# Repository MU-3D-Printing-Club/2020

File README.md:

# 2020
Meetings 2pm Thursday in E3508.

[Link to Ada Assembly instructions](https://openbionicslabs.com/obtutorials/ada-v1-assembly)

## Updates 2/27/2020
- Please remember to always **PULL FROM ORIGIN** and make a new branch before you make edits.
- Installed gitHub, Eagle, and SolidWorks on lab computer

## V2
Stuart's ARM board and probably Rust code.
- [x] Ask Dr. Gillis for review. (JD)
- [ ] Get rust code running for servos on discovery board. PWM libraries and also [potentiometer controlled feedback](https://www.actuonix.com/Actuonix-PQ-12-P-Linear-Actuator-p/pq12-p.htm). (Chris/Jake/Stuart/James/Matt)
- [x] Identify which rust-compatible chip to buy. (Jake/Stuart)
## V1
### V1.3 

Added [boost regulator](http://ww1.microchip.com/downloads/en/DeviceDoc/20005572A.pdf) in addition to 1.2 changes.  
- [ ] Review Ahmad's suggestions. Look in "Regulator" branch. (Jake/Ethan)
- [ ] Make Vcc route bigger.
### V1.2
Added [LiPo](https://cdn.sparkfun.com/assets/learn_tutorials/6/9/5/MCP738312.pdf) charger.

- [ ] Solder chip and resistors on.
- [ ] Burn bootloader and code. See if it works.
- [ ] Research new trigger algorithm. (James/Matt)
- [ ] Research custom myoelectric sensor. (Rosie)
- [ ] PALM DESIGN! (Chris, Hannah, Colm)
### V1.1
Reorganized PCB. Larger back cover.

- [ ] Document
- [ ] SHIP.
- [x] Tie knots. (Jack)
- [x] Solder myoelectric in.
- [x] Attach servos.
- [x] Print back cover.
- [x] Epoxy screw in.
- [x] Get the programmer out of reset mode. (Stuart)

### V1.0
From December. Broke because of lack and space/organization in back cover.

## V0
Bare bones code and prototype back cover. Cannot find Eagle file. Only legend speaks of this.

<pre>
.
├── Datasheets
│   ├── Actuonix+PQ12+Datasheet.pdf
│   ├── MCP73831.pdf
│   └── STM32F303.pdf
├── Myosensor
│   ├── Myosense.v1.brd
│   └── Myosense.v1.sch
├── Old
│   ├── Eagle Libraries
│   │   └── 3DPC.lbr
│   ├── Jig Components
│   │   ├── Legiment Jig.SLDPRT
│   │   └── Legiment Jig.STL
│   ├── eletronics test bed
│   │   ├── 400 point breadboard holder.stl
│   │   ├── STM32F3DISCOVERY holder.stl
│   │   ├── actuonix PQ12 servo holder.stl
│   │   ├── battery holder.stl
│   │   └── electronics v1.0 holder.stl
│   ├── v0.0
│   │   ├── SolidWorks
│   │   │   ├── Backcover 12-6-19.SLDPRT
│   │   │   └── Backcover 12-6-19.STL
│   │   ├── myoFlex-Original
│   │   │   └── myoFlex.ino
│   │   └── pcb
│   │       ├── circuitdraft.brd
│   │       ├── circuitdraft.sch
│   │       └── eagle.epf
│   ├── v0.1
│   │   └── PCB
│   │       ├── circuitdraft.brd
│   │       ├── circuitdraft.sch
│   │       └── eagle.epf
│   ├── v1.0
│   │   ├── PCB
│   │   │   ├── circuitdraft.brd
│   │   │   ├── circuitdraft.sch
│   │   │   └── eagle.epf
│   │   ├── PCB Libraries
│   │   │   ├── SamacSys_Parts.lbr
│   │   │   ├── TPS54627DDAR.lbr
│   │   │   ├── charger.lbr
│   │   │   ├── ind2.lbr
│   │   │   ├── inductor.lbr
│   │   │   ├── mega32U4.lbr
│   │   │   ├── microchip-update.lbr
│   │   │   └── powerPad.lbr
│   │   ├── SolidWorks
│   │   │   ├── 191216_Backcover_JD.SLDPRT
│   │   │   └── 191216_Backcover_JD.STL
│   │   ├── circuitdraft.txt
│   │   └── mainCode
│   │       └── mainCode.ino
│   ├── v1.1
│   │   ├── CAD
│   │   │   ├── 02_18_2020_BackcoverC.SLDPRT
│   │   │   ├── 02_18_2020_BackcoverF.SLDPRT
│   │   │   ├── 02_18_2020_BackcoverF.STL
│   │   │   ├── 2020_03_02_BackcoverShell.SLDPRT
│   │   │   ├── 203101_Backcover.SLDPRT
│   │   │   ├── Front Face Palm Screen Capture.PNG
│   │   │   ├── New Palm STL.STL
│   │   │   ├── New Palm.SLDPRT
│   │   │   ├── R_palm.SLDPRT
│   │   │   └── R_palm.stl
│   │   ├── Code
│   │   │   ├── Blink
│   │   │   │   └── Blink.ino
│   │   │   ├── helloWorld
│   │   │   │   └── helloWorld.ino
│   │   │   ├── mainCode
│   │   │   │   └── mainCode.ino
│   │   │   └── servoTest
│   │   │       └── servoTest.ino
│   │   └── PCB
│   │       ├── circuitdraft.brd
│   │       ├── circuitdraft.sch
│   │       └── eagle.epf
│   ├── v1.2
│   │   ├── Notes.txt
│   │   ├── PCB
│   │   │   ├── circuitdraft.brd
│   │   │   ├── circuitdraft.sch
│   │   │   └── eagle.epf
│   │   ├── mainCode
│   │   │   └── mainCode.ino
│   │   └── testLiPoCharger
│   │       └── testLiPoCharger.ino
│   ├── v1.3
│   │   ├── circuitdraft.brd
│   │   └── circuitdraft.sch
│   ├── v2.0
│   │   └── PCB
│   │       ├── Hand v2.0 parts.lib
│   │       ├── Hand v2.0-cache.lib
│   │       ├── Hand v2.0-rescue.dcm
│   │       ├── Hand v2.0.kicad_pcb
│   │       ├── Hand v2.0.kicad_pcb-bak
│   │       ├── Hand v2.0.net
│   │       ├── Hand v2.0.sch
│   │       ├── Hand v2.0.sch-bak
│   │       ├── fp-info-cache
│   │       ├── hand parts.bck
│   │       ├── hand parts.dcm
│   │       └── sym-lib-table
│   └── v2.1
│       └── PCB
│           ├── 2020-02-01_02-22-13
│           │   ├── 2020-02-01_02-22-13.lib
│           │   ├── footprints.pretty
│           │   │   └── STM32F302_303C2.kicad_mod
│           │   └── readme.txt
│           ├── Hand v2.1 parts.lib
│           ├── Hand v2.1-cache.lib
│           ├── Hand v2.1-rescue.dcm
│           ├── Hand v2.1-rescue.lib
│           ├── Hand v2.1.kicad_pcb
│           ├── Hand v2.1.kicad_pcb-bak
│           ├── Hand v2.1.net
│           ├── Hand v2.1.sch
│           ├── Hand v2.1.sch-bak
│           ├── fp-info-cache
│           ├── hand parts.bck
│           ├── hand parts.dcm
│           └── sym-lib-table
├── README.md
├── tree.txt
├── treeCMD.txt
└── v3.0
    └── hand v3.0
        ├── Hand Parts.bck
        ├── Hand Parts.dcm
        ├── Hand Parts.lib
        ├── fp-info-cache
        ├── hand v3.0-cache.lib
        ├── hand v3.0.kicad_pcb
        ├── hand v3.0.sch
        ├── hand v3.0.sch-bak
        ├── hand v3.xml
        └── sym-lib-table

38 directories, 103 files

</pre>
tree -I "*.pro|*.b#?|*.s#?|*.l?|*.job" -o tree.txt

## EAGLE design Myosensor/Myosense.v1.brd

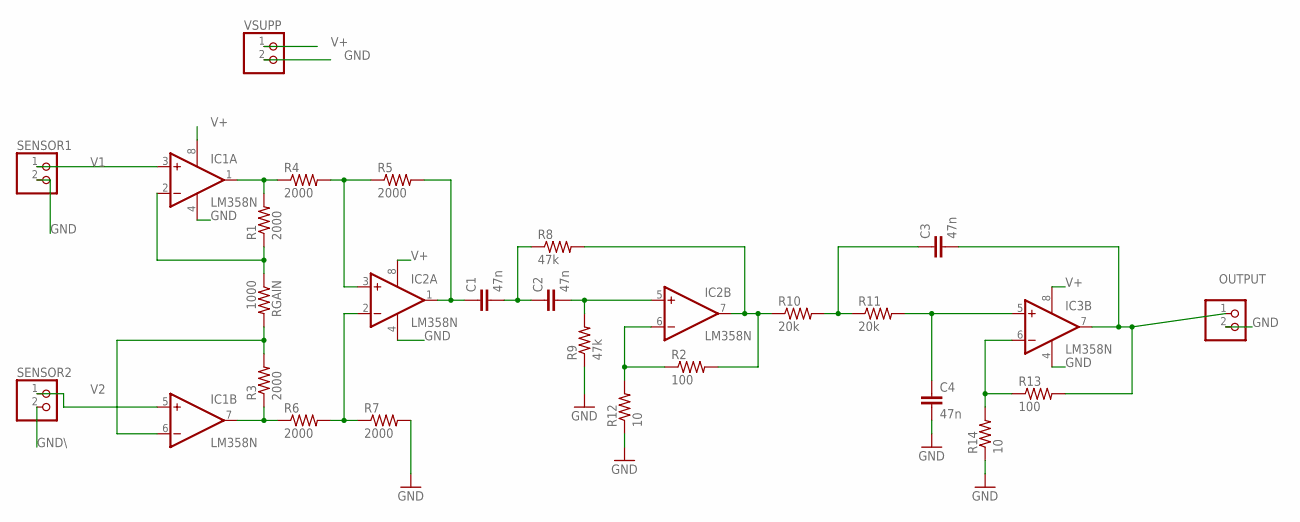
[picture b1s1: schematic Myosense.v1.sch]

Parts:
C1, C2, C3, C4: 47n; C2.5-3
IC1, IC2, IC3: LM358N; DIL08
OUTPUT: PINHD-1X2; 1X02
R1, R3, R4, R5, R6, R7: 2000; 0204/5
R2, R13: 100; 0204/5
R8, R9: 47k; 0204/5
R10, R11: 20k; 0204/5
R12, R14: 10; 0204/5
RGAIN: 1000; 0204/5
SENSOR1, SENSOR2: PINHD-1X2; 1X02
VSUPP: PINHD-1X2; 1X02

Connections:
GND: C4.2, IC1.4 (V-), IC2.4 (V-), IC3.4 (V-), OUTPUT.2, R7.2, R9.1, R12.1, R14.1, SENSOR1.2, VSUPP.2
GND\: SENSOR2.2
unnamed: IC1.1 (OUT), R1.2, R4.1
unnamed: IC1.2 (-IN), R1.1, RGAIN.1
unnamed: IC1.6 (-IN), R3.2, RGAIN.2
unnamed: IC2.3 (+IN), R4.2, R5.1
unnamed: IC1.7 (OUT), R3.1, R6.1
unnamed: IC2.2 (-IN), R6.2, R7.1
unnamed: C1.1, IC2.1 (OUT), R5.2
unnamed: C1.2, C2.1, R8.1
unnamed: C2.2, IC2.5 (+IN), R9.2
unnamed: IC2.7 (OUT), R2.2, R8.2, R10.1
unnamed: IC2.6 (-IN), R2.1, R12.2
unnamed: C3.1, R10.2, R11.1
unnamed: C4.1, IC3.5 (+IN), R11.2
unnamed: IC3.6 (-IN), R13.1, R14.2
unnamed: C3.2, IC3.7 (OUT), OUTPUT.1, R13.2
V1: IC1.3 (+IN), SENSOR1.1
V2: IC1.5 (+IN), SENSOR2.1
V+: IC1.8 (V+), IC2.8 (V+), IC3.8 (V+), VSUPP.1

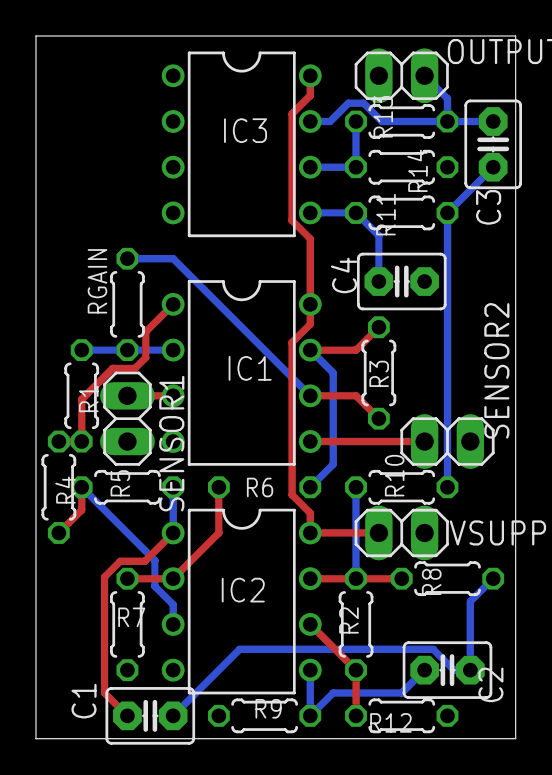
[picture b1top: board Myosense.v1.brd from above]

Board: 2 copper layers, 26.7 x 39.0 mm, 26 parts (1 on the bottom side), 19 nets.

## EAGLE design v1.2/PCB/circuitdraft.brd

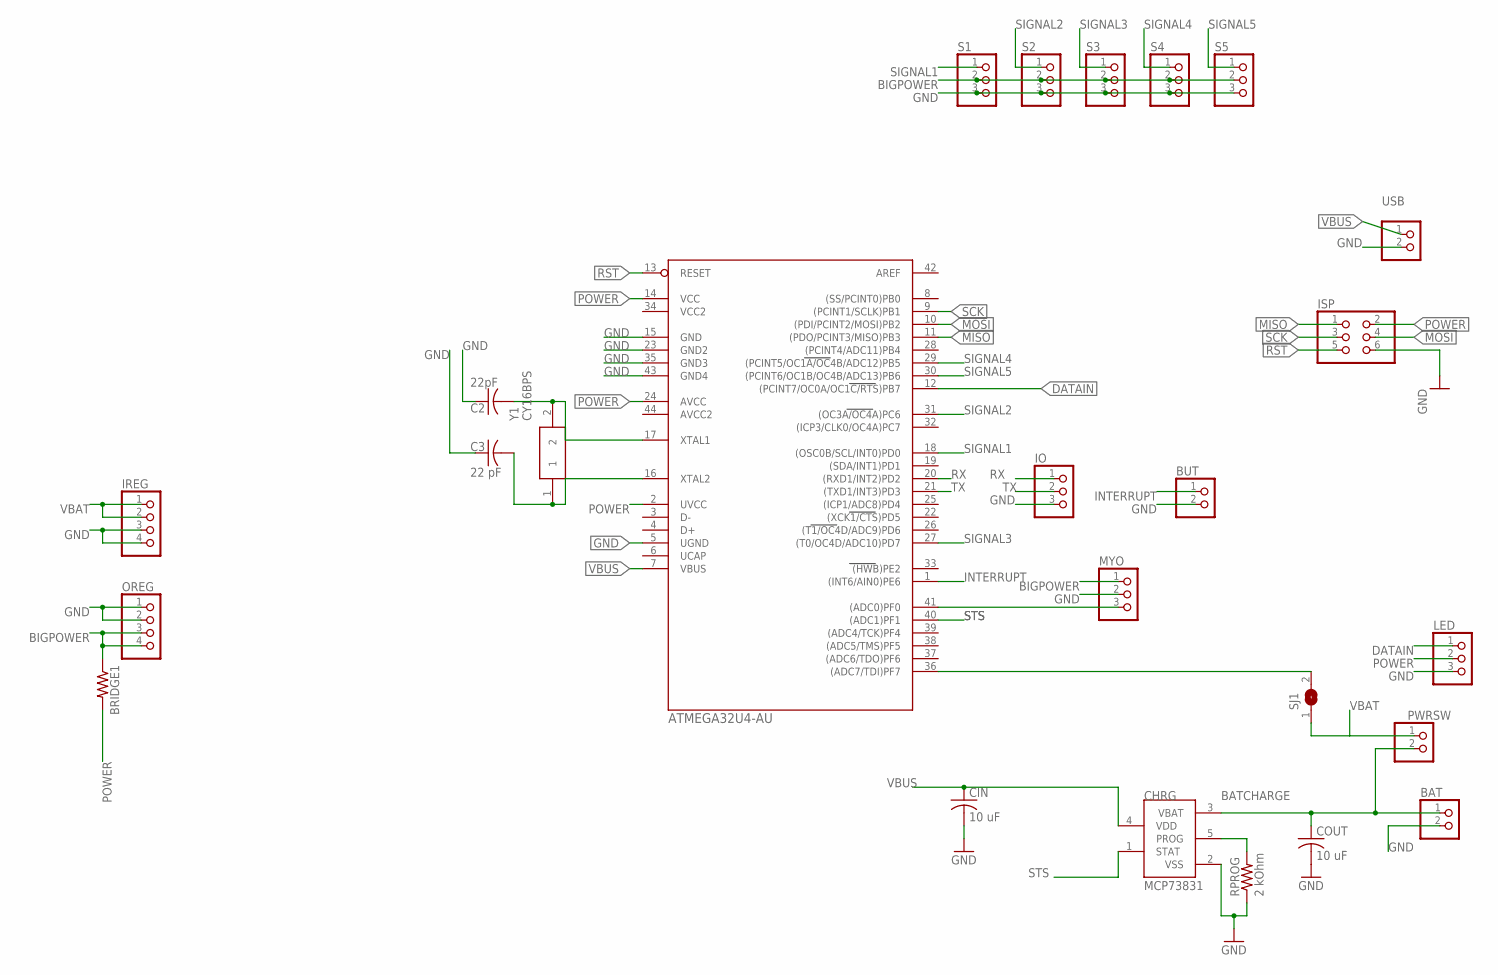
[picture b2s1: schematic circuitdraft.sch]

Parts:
BAT: PINHD-1X2; 1X02
BRIDGE1: R-US_M0805; M0805
BUT: PINHD-1X2; 1X02
C2: 22pF; C025-024X044
C3: 22 pF; C025-024X044
CHRG: MCP73831; SOT23-5L
CIN: 10 uF; C0603
COUT: 10 uF; C0603
IO: PINHD-1X3; 1X03
IREG: PINHD-1X4; 1X04
ISP: PINHD-2X3; 2X03
LED: PINHD-1X3; 1X03
MYO: PINHD-1X3; 1X03
OREG: PINHD-1X4; 1X04
PWRSW: PINHD-1X2; 1X02
RPROG: 2 kOhm; R0603
S1, S2, S3, S4, S5: PINHD-1X3; 1X03
SJ1: SJ
U$1: ATMEGA32U4-AU; TQFP44
USB: PINHD-1X2; 1X02
Y1: CY16BPS

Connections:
BATCHARGE: BAT.1, CHRG.3 (VBAT), COUT.1, PWRSW.2
BIGPOWER: BRIDGE1.1, MYO.1, OREG.3, OREG.4, S1.2, S2.2, S3.2, S4.2, S5.2
DATAIN: LED.1, U$1.12 ((PCINT7/OC0A/OC1C/RTS)PB7)
GND: BAT.2, BUT.2, C2.1, C3.1, CHRG.2 (VSS), CIN.2, COUT.2, IO.3, IREG.3, IREG.4, ISP.6, LED.3, MYO.2, OREG.1, OREG.2, RPROG.1, S1.3, S2.3, S3.3, S4.3, S5.3, U$1.5 (UGND), U$1.15 (GND), U$1.23 (GND2), U$1.35 (GND3), U$1.43 (GND4), USB.2
INTERRUPT: BUT.1, U$1.1 ((INT6/AIN0)PE6)
MISO: ISP.1, U$1.11 ((PDO/PCINT3/MISO)PB3)
MOSI: ISP.4, U$1.10 ((PDI/PCINT2/MOSI)PB2)
unnamed: MYO.3, U$1.41 ((ADC0)PF0)
unnamed: SJ1.2, U$1.36 ((ADC7/TDI)PF7)
unnamed: CHRG.5 (PROG), RPROG.2
unnamed: C2.2, U$1.17 (XTAL1), Y1.2
unnamed: C3.2, U$1.16 (XTAL2), Y1.1
POWER: BRIDGE1.2, ISP.2, LED.2, U$1.2 (UVCC), U$1.14 (VCC), U$1.24 (AVCC)
RST: ISP.5, U$1.13 (RESET)
RX: IO.1, U$1.20 ((RXD1/INT2)PD2)
SCK: ISP.3, U$1.9 ((PCINT1/SCLK)PB1)
SIGNAL1: S1.1, U$1.18 ((OSC0B/SCL/INT0)PD0)
SIGNAL2: S2.1, U$1.31 ((OC3A/OC4A)PC6)
SIGNAL3: S3.1, U$1.27 ((T0/OC4D/ADC10)PD7)
SIGNAL4: S4.1, U$1.29 ((PCINT5/OC1A/OC4B/ADC12)PB5)
SIGNAL5: S5.1, U$1.30 ((PCINT6/OC1B/OC4B/ADC13)PB6)
STS: CHRG.1 (STAT), U$1.40 ((ADC1)PF1)
TX: IO.2, U$1.21 ((TXD1/INT3)PD3)
VBAT: IREG.1, IREG.2, PWRSW.1, SJ1.1
VBUS: CHRG.4 (VDD), CIN.1, U$1.7 (VBUS), USB.1

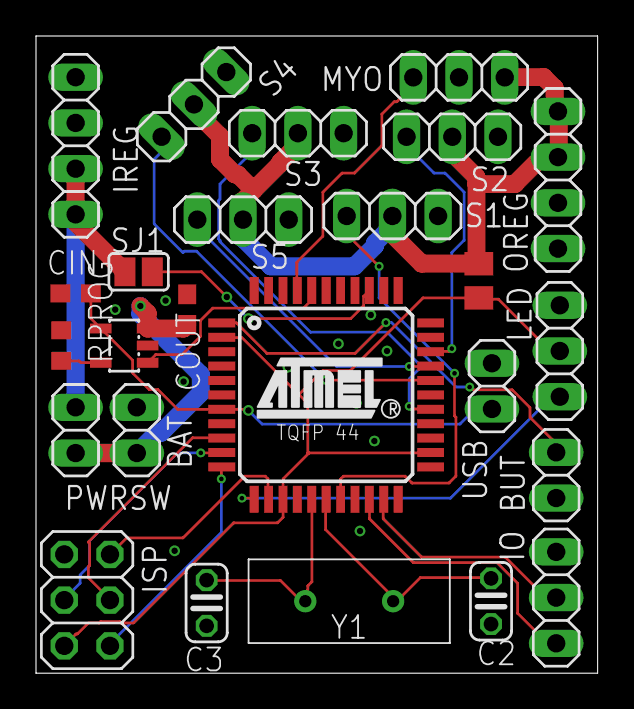
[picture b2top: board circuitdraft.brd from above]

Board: 2 copper layers, 31.2 x 35.4 mm, 25 parts (0 on the bottom side), 25 nets.

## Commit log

2020-01-25 Reorganized
2020-01-25 Added old files
2020-01-25 Set theme jekyll-theme-minimal
2020-01-25 renamed directories added v0.1 pcb
2020-01-25 added v1.1 and v2.0 boards
2020-01-25 added version silkscreen to v1.1 board
2020-01-25 v1.1 shifted silkscreen text
2020-01-25 v2.0 added version silkscreen and renamed files
2020-01-26 Add microchip eagle library
2020-01-26 Began creatin custom libraries
    Sorry chris for pushing directly to master. I will stop doin gthis now
2020-01-27 v2.0 fixed file naming issues
2020-01-31 readded v1.2 because oops
2020-02-01 Added switch. Passes DRC
    Final 1.2
2020-02-01 Update 191216_Backcover_JD.SLDPRT
    Added 5mm of height to exterior wall.
2020-02-01 Added jack's cover
    hope this works
2020-02-01 Added palm .stl
2020-02-01 Renamed Folder SolidWorks
2020-02-01 Update Readme. Rename Backover
2020-02-01 hi chris
2020-02-01 began swapping arm chips
2020-02-01 rename 2.0 to 2.1 for chip change
2020-02-01 undo oops by readding v2.0
2020-02-01 created servo holder for test bed
2020-02-02 finished adding STM32F303VCT6
2020-02-02 cleaned up silkscreen and updated version on silkscreen
2020-02-03 Removed Back Shell
2020-02-03 refined test bed mounts
2020-02-04 removed need for supports and made discovery board holder shorter and shifted holes
2020-02-04 Added code to 1.2
2020-02-05 Update eagle library
2020-02-05 Added MIC to Lib
2020-02-06 I wrote a test messge
2020-02-06 pooppoo
2020-02-06 Added MIC regulator
2020-02-09 connected unused IO pins on MCU to ground
2020-02-18 Create blink
2020-02-20 Added solid parts
2020-02-20 Updated 2_18_2020_F back cover
2020-02-20 Saved R_Palm file to a SLDPRT file
2020-02-20 Started moving timing chip
2020-02-21 Started ahmad's changes
2020-02-23 Created a SLDPRT file to manipulte in Blender. Foundation of new plam.
2020-02-27 New Palm has been updated
2020-02-27 restored files
2020-02-29 code
2020-03-01 Easier to print
2020-03-03 Jacks changes
2020-03-03 fix thumb pin
2020-03-03 added reset pull-up resistor
2020-03-03 zone refill
2020-03-07 new palm
2020-03-08 enabled regulators and removed unneeded part
2020-03-08 updated name of battery to be clearer
2020-03-09 Added dimensions for servo inlets in the new palm design
2020-03-12 Changed so servo does not grab so far
2020-03-18 test
2020-03-18 Added LM358
2020-04-11 added file tree
2020-04-12 Schematic1
2020-04-13 Worked on myosensor
2020-04-29 Myosensor board and library change
2020-05-21 Updated myosensor
2020-05-31 created v3 project
2020-06-03 testing 1.2 charger
2020-06-04 Added datasheets
2020-06-05 started on power for 3.0
2020-06-06 motor and motor drivers configured
2020-06-17 Housekeeping
2020-06-17 housekeeping part II
2020-06-29 added some datasheets
2020-06-30 Added some documents
2020-07-07 added bookmark
2020-08-13 added manual
2020-09-17 added bom
